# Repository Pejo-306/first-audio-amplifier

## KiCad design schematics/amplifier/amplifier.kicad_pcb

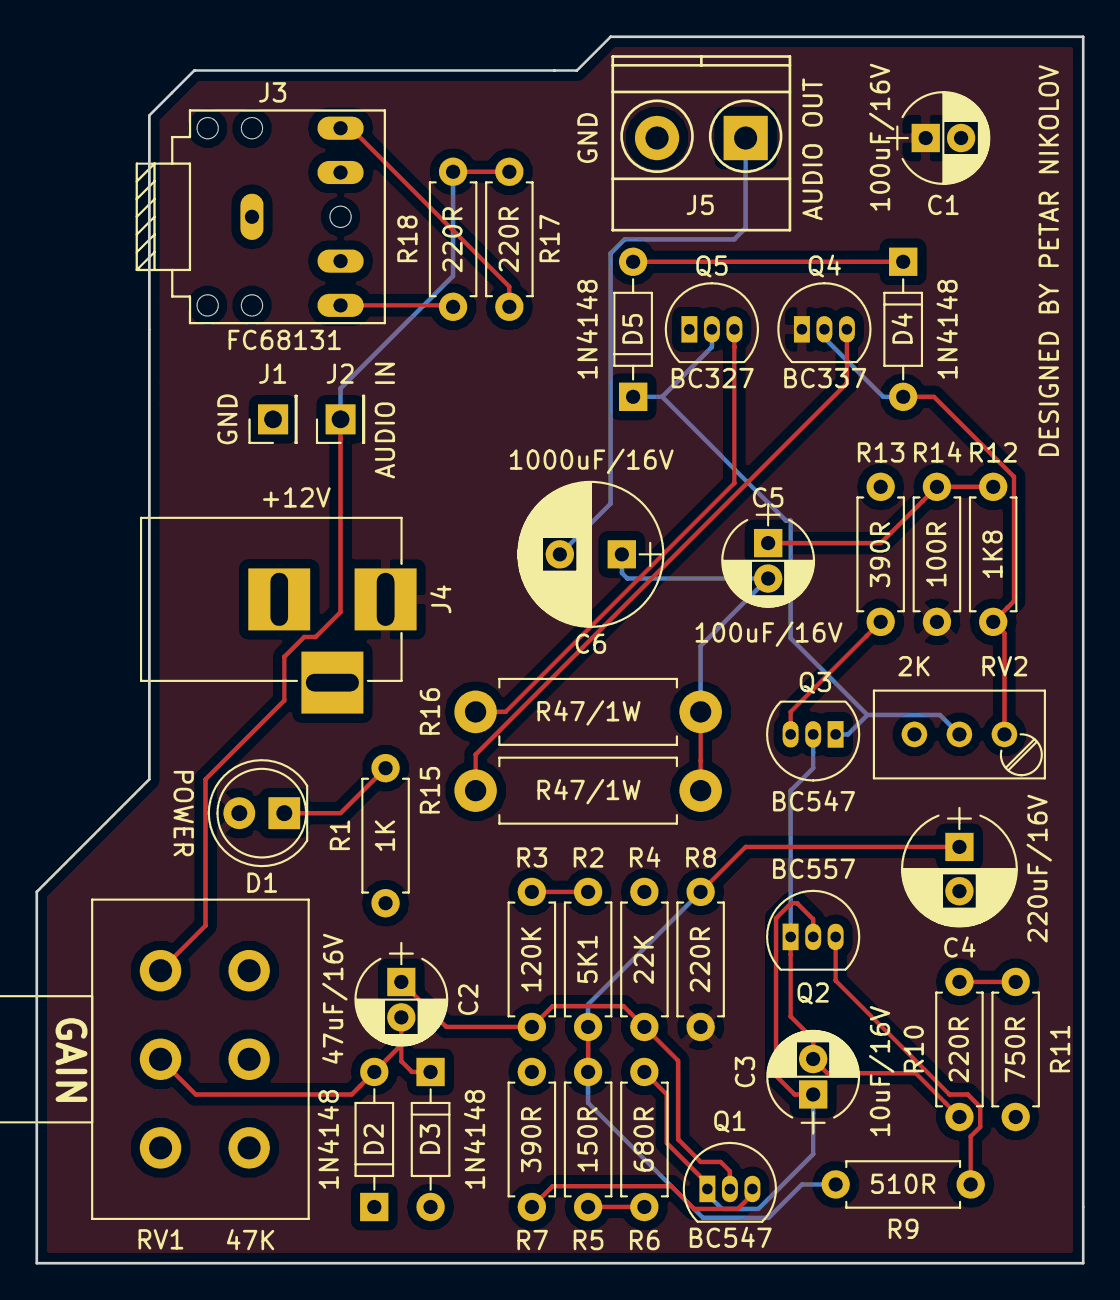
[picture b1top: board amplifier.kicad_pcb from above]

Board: 2 copper layers, 59.1 x 69.2 mm, 41 parts (0 on the bottom side), 25 nets.

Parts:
C1, C5: 100uF/16V; CP_Radial_D5.0mm_P2.00mm
C2: 47uF/16V; CP_Radial_D5.0mm_P2.00mm
C3: 10uF/16V; CP_Radial_D5.0mm_P2.00mm
C4: 220uF/16V; CP_Radial_D6.3mm_P2.50mm
C6: 1000uF/16V; CP_Radial_D8.0mm_P3.50mm
D1: LED; LED_D5.0mm
D2, D3, D4, D5: 1N4148; D_DO-35_SOD27_P7.62mm_Horizontal
J1, J2: Conn_01x01_Male; Pin_Header_Straight_1x01_Pitch2.54mm
J3: FC68131; FC68131-5P
J4: Jack-DC; BARREL_JACK
J5: Screw_Terminal_01x02; TerminalBlock_Phoenix_MKDS1.5-2pol
Q1, Q3: BC547; TO-92_Inline_Narrow_Oval
Q2: BC557; TO-92_Inline_Narrow_Oval
Q4: BC337; TO-92_Inline_Narrow_Oval
Q5: BC327; TO-92_Inline_Narrow_Oval
R1: 1K; R_Axial_DIN0207_L6.3mm_D2.5mm_P7.62mm_Horizontal
R2: 5K1; R_Axial_DIN0207_L6.3mm_D2.5mm_P7.62mm_Horizontal
R3: 120K; R_Axial_DIN0207_L6.3mm_D2.5mm_P7.62mm_Horizontal
R4: 22K; R_Axial_DIN0207_L6.3mm_D2.5mm_P7.62mm_Horizontal
R5: 150R; R_Axial_DIN0207_L6.3mm_D2.5mm_P7.62mm_Horizontal
R6: 680R; R_Axial_DIN0207_L6.3mm_D2.5mm_P7.62mm_Horizontal
R7, R13: 390R; R_Axial_DIN0207_L6.3mm_D2.5mm_P7.62mm_Horizontal
R8, R10, R17, R18: 220R; R_Axial_DIN0207_L6.3mm_D2.5mm_P7.62mm_Horizontal
R9: 510R; R_Axial_DIN0207_L6.3mm_D2.5mm_P7.62mm_Horizontal
R11: 750R; R_Axial_DIN0207_L6.3mm_D2.5mm_P7.62mm_Horizontal
R12: 1K8; R_Axial_DIN0207_L6.3mm_D2.5mm_P7.62mm_Horizontal
R14: 100R; R_Axial_DIN0207_L6.3mm_D2.5mm_P7.62mm_Horizontal
R15, R16: R47/1W; R_Axial_DIN0411_L9.9mm_D3.6mm_P12.70mm_Horizontal
RV1: 47K; Potentiometer_Alps_RK163_Double_Vertical
RV2: 2K; Potentiometer_Trimmer_Bourns_3296W

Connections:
+12V: C1.1, D1.2, J4.1, Q4.1, R8.1, R14.1
/AUDIO_IN: J2.1, R17.1, R18.2, RV1.1
/AUDIO_OUT: C6.2, J5.1
GND: C1.2, C4.2, D2.1, D3.2, J1.1, J3.1, J4.2, J5.2, Q5.1, R1.2, R4.2, R7.2, R11.2, R13.2, RV1.3
unnamed: C2.1, Q1.2, R3.2, R4.1
unnamed: C2.2, D2.2, D3.1, RV1.2
unnamed: C3.1, Q1.1, Q2.2, R6.2
unnamed: C3.2, Q2.1, Q3.2, R10.1
unnamed: C4.1, R2.1, R5.1, R8.2, R9.1
unnamed: C5.1, R12.1, R14.2
unnamed: C5.2, C6.1, R15.2, R16.1
unnamed: D1.1, R1.1
unnamed: D4.1, D5.2
unnamed: D4.2, Q4.2, R12.2, RV2.1
unnamed: D5.1, Q3.1, Q5.2, RV2.2
unnamed: J3.2, R18.1
unnamed: J3.5, R17.2
unnamed: Q1.3, R7.1
unnamed: Q2.3, R9.2
unnamed: Q3.3, R13.1
unnamed: Q4.3, R15.1
unnamed: Q5.3, R16.2
unnamed: R2.2, R3.1
unnamed: R5.2, R6.1
unnamed: R10.2, R11.1

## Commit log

2018-08-07 Add main amplifier schematics
2018-08-14 Finalize amplifier schematic design
    This commit includes the finalized version of this project's audio
    amplifier.
    Additions:
    - changed all 'Earth symbols' to 'GND' symbols
    - add a dc jack to power the circuit
    - add an audio jack to play music
2018-08-14 Use custom audio jack footprint and symbol from SnapEDA
2018-08-15 Layout the components on the board
    Also, there is a slight change in the project's schematic: the stereo
    input from the audio jack has been converted to mono input via the
    appropriate resistors and connections.
2018-10-12 Redo calculations on (again...) the output and driver stages
    I have committed a spreadsheet which can automatically calculate
    the output and driver stages of this project's amplifier. Some
    parameters have to manually be assigned.
2018-10-13 Fix calculation in Output Stage
    One of the driver stage's constraint had two problems:
    - the GBP of the transistor is about 280 MHz at the given conditions
    - the calculation was using a wrong parameter: 'hFE' instead of 'hfe'
2018-10-13 Commit microphone preamp calculations
2018-10-13 Change the wanted lower frequency to 50 Hz
    Also, the preamp's design now includes an input decoupling capacitor
    (designated by 'C2').
2018-10-14 Update lower frequency requirements in calculations
    The lowest frequency that the amplifier should operate on is now 100 Hz
    (from 50 Hz). This frequency has been chosen because:
    - frequencies below 100 Hz barely produce an audible effect;
    - increasing the supported lower frequency entails using lower value
    capacitors.
2018-10-14 [Schematics] Design output stage amplifier
2018-10-14 [Schematics] Add mic preamp
2018-10-14 [Schematics] Add a few features
    - added reverse polarity protection;
    - designed a simple audio mixer with a few OpAmps;
    - added screw terminals for output;
    - added audio jacks for input;
    - annotated schematic.
2018-10-15 Rename amplifier circuit project files
    The amplifier circuit's project has been renamed from
    'FirstAudioAmplifier' to 'amplifier'.
2018-10-15 Ignore temporary LibreOffice files
2018-10-15 [Schematics] Commit microphone circuit schematic
2018-10-15 [PCB] Added custom footprint of condenser microphone (ECM-30B)
2018-10-16 [Schematics] Associate footprints with amplifier's components
2018-10-16 [Schematics] Associate footprints with microphone circuit's components
    Also, a 3 pin connector has been added, which should lie on the pcb and
    connect to the audio connector via wires.
